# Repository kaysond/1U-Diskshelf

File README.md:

# 1U-DiskShelf
A 3D-Printable 1U Disk Shelf (4 bays) With Custom SATA Backplane

Board files can be found in the Backplane PCB directory.

Models can be found on [MakerWorld](https://makerworld.com/en/models/1570200-1u-disk-shelf-19-inch-4-bay-10-inch-2-bay) or see the Models directory for CAD files

# License
This project is released under the CC BY-NC-SA 4.0 license. See LICENSE.txt or https://creativecommons.org/licenses/by-nc-sa/4.0/

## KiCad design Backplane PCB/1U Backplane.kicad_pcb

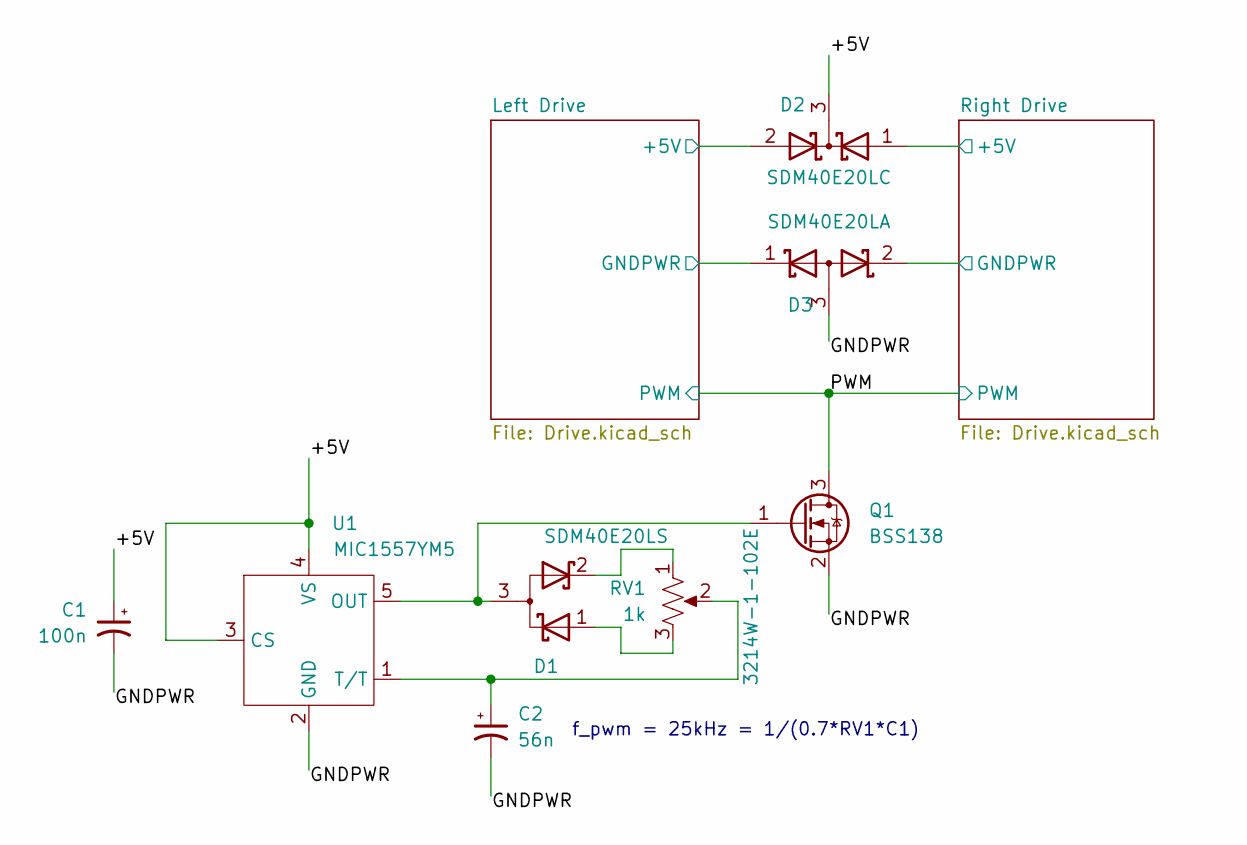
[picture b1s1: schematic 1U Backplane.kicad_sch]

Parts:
C1: 100n; C_0603_1608Metric_Pad1.08x0.95mm_HandSolder
C2: 56n; C_0603_1608Metric_Pad1.08x0.95mm_HandSolder
D1: SDM40E20LS; SOT-23
D2: SDM40E20LC; SOT-23
D3: SDM40E20LA; SOT-23
Q1: BSS138; SOT-23
RV1: 1k; Potentiometer_Bourns_3214W_Vertical; Part No 3214W-1-102E
U1: MIC1557YM5; SOT-23-5

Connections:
/+5V: C1.1, D2.3 (K), U1.3 (CS), U1.4 (VS)
/GNDPWR: C1.2, C2.2, D3.3 (A), Q1.2 (S), U1.2 (GND)
/Left Drive/+5V: D2.2 (A); also elsewhere on the board
/Left Drive/GNDPWR: D3.1 (K); also elsewhere on the board
/PWM: Q1.3 (D); also elsewhere on the board
/Right Drive/+5V: D2.1 (A); also elsewhere on the board
/Right Drive/GNDPWR: D3.2 (K); also elsewhere on the board
unnamed: D1.3 (A), Q1.1 (G), U1.5 (OUT)
unnamed: D1.1 (K), RV1.3
unnamed: D1.2 (K), RV1.1
unnamed: C2.1, RV1.2, U1.1 (T/T)

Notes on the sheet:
f_pwm = 25kHz = 1/(0.7*RV1*C1)

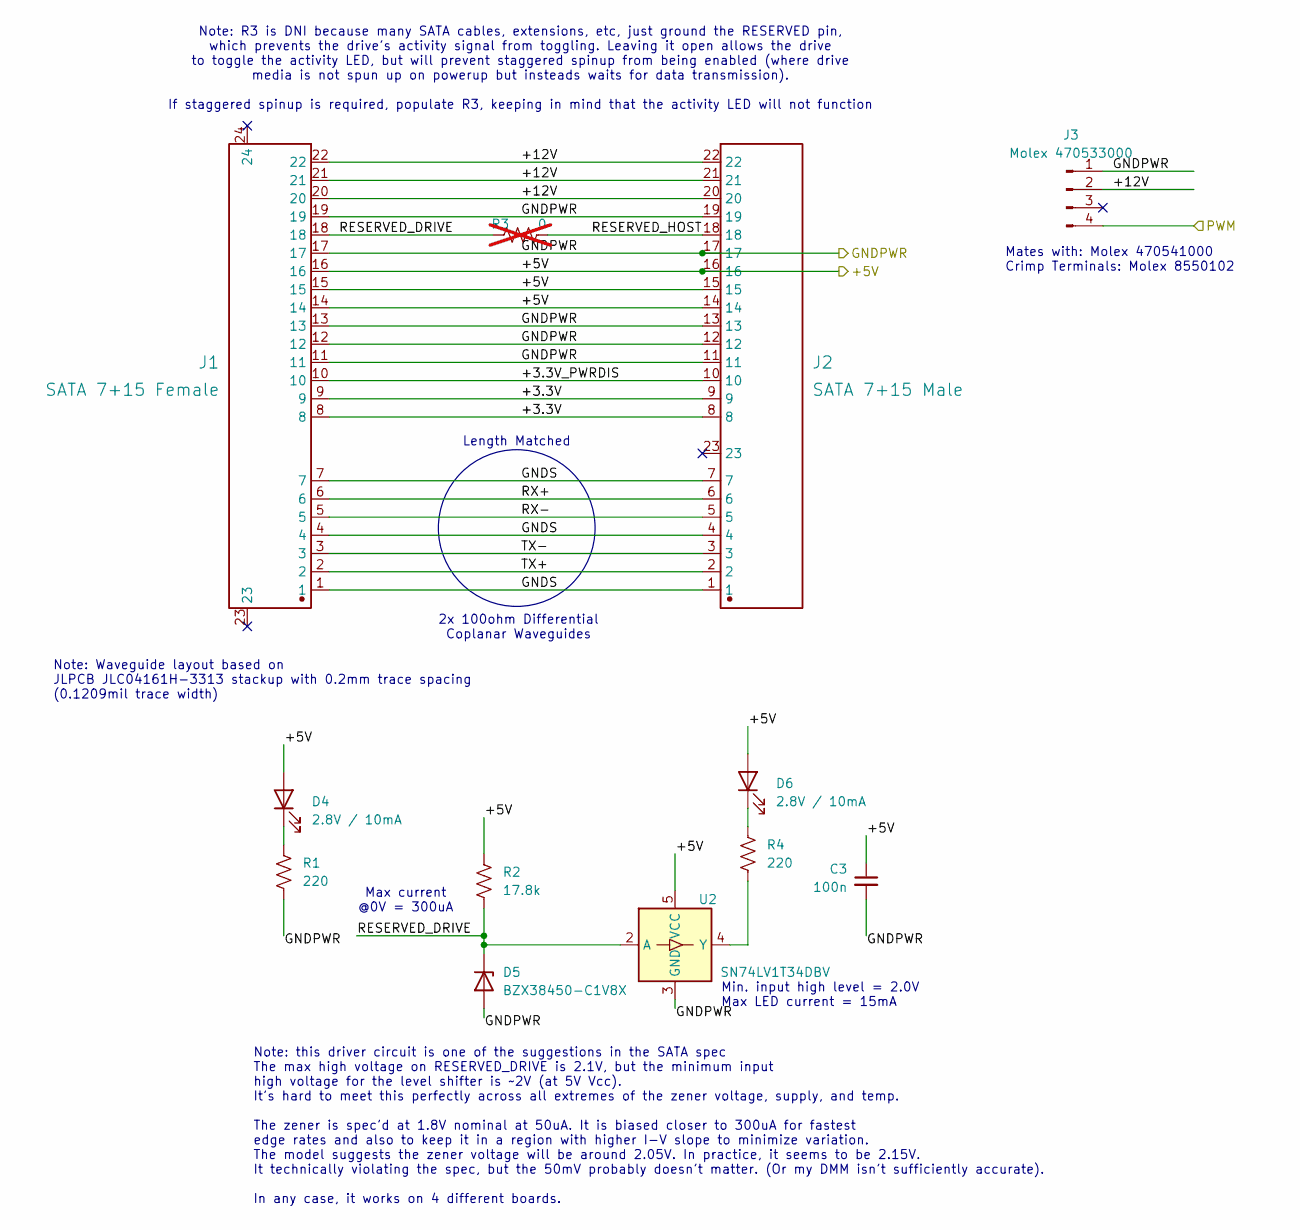
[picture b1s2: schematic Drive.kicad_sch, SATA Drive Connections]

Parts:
C3: 100n; C_0603_1608Metric_Pad1.08x0.95mm_HandSolder
D4, D6: 2.8V / 10mA; LED_0603_1608Metric_Pad1.05x0.95mm_HandSolder
D5: BZX38450-C1V8X; D_SOD-323_HandSoldering
J1: SATA 7+15 Female; CONN-TH_SATA7-15-TYPE-B; Manufacturer Part SATA 7+15 TYPE-B
J2: SATA 7+15 Male; CONN-TH_SATA7-15-TYPE-A; Manufacturer Part SATA 7+15 TYPE-A
J3: Molex 470533000; Molex_KK-254_AE-6410-04A_1x04_P2.54mm_Vertical
R1, R4: 220; R_0603_1608Metric_Pad0.98x0.95mm_HandSolder
R2: 17.8k; R_0603_1608Metric_Pad0.98x0.95mm_HandSolder
R3: 0; R_0402_1005Metric; not fitted
U2: SN74LV1T34DBV; SOT-23-5

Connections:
/Left Drive/+3.3V: J1.8, J1.9, J2.8, J2.9
/Left Drive/+3.3V_PWRDIS: J1.10, J2.10
/Left Drive/+5V: C3.1, D4.2 (A), D6.2 (A), J1.14, J1.15, J1.16, J2.14, J2.15, J2.16, R2.1, U2.5 (VCC); also elsewhere on the board
/Left Drive/+12V: J1.20, J1.21, J1.22, J2.20, J2.21, J2.22, J3.2
/Left Drive/GNDPWR: C3.2, D5.2 (A), J1.11, J1.12, J1.13, J1.17, J1.19, J2.11, J2.12, J2.13, J2.17, J2.19, J3.1, R1.2, U2.3 (GND); also elsewhere on the board
/Left Drive/GNDS: J1.1, J1.4, J1.7, J2.1, J2.4, J2.7
/Left Drive/RESERVED_DRIVE: D5.1 (K), J1.18, R2.2, R3.1, U2.2 (A)
/Left Drive/RESERVED_HOST: J2.18, R3.2
/Left Drive/RX+: J1.6, J2.6
/Left Drive/RX-: J1.5, J2.5
/Left Drive/TX+: J1.2, J2.2
/Left Drive/TX-: J1.3, J2.3
/PWM: J3.4; also elsewhere on the board
unnamed: D4.1 (K), R1.1
unnamed: D6.1 (K), R4.1
unnamed: R4.2, U2.4 (Y)

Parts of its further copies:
C4: 100n; C_0603_1608Metric_Pad1.08x0.95mm_HandSolder
D7, D9: 2.8V / 10mA; LED_0603_1608Metric_Pad1.05x0.95mm_HandSolder
D8: BZX38450-C1V8X; D_SOD-323_HandSoldering
J4: SATA 7+15 Female; CONN-TH_SATA7-15-TYPE-B; Manufacturer Part SATA 7+15 TYPE-B
J5: SATA 7+15 Male; CONN-TH_SATA7-15-TYPE-A; Manufacturer Part SATA 7+15 TYPE-A
J6: Molex 470533000; Molex_KK-254_AE-6410-04A_1x04_P2.54mm_Vertical
R5, R8: 220; R_0603_1608Metric_Pad0.98x0.95mm_HandSolder
R6: 17.8k; R_0603_1608Metric_Pad0.98x0.95mm_HandSolder
R7: 0; R_0402_1005Metric; not fitted
U3: SN74LV1T34DBV; SOT-23-5

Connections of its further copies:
/PWM: J6.4; also elsewhere on the board
/Right Drive/+3.3V: J4.8, J4.9, J5.8, J5.9
/Right Drive/+3.3V_PWRDIS: J4.10, J5.10
/Right Drive/+5V: C4.1, D7.2 (A), D9.2 (A), J4.14, J4.15, J4.16, J5.14, J5.15, J5.16, R6.1, U3.5 (VCC); also elsewhere on the board
/Right Drive/+12V: J4.20, J4.21, J4.22, J5.20, J5.21, J5.22, J6.2
/Right Drive/GNDPWR: C4.2, D8.2 (A), J4.11, J4.12, J4.13, J4.17, J4.19, J5.11, J5.12, J5.13, J5.17, J5.19, J6.1, R5.2, U3.3 (GND); also elsewhere on the board
/Right Drive/GNDS: J4.1, J4.4, J4.7, J5.1, J5.4, J5.7
/Right Drive/RESERVED_DRIVE: D8.1 (K), J4.18, R6.2, R7.1, U3.2 (A)
/Right Drive/RESERVED_HOST: J5.18, R7.2
/Right Drive/RX+: J4.6, J5.6
/Right Drive/RX-: J4.5, J5.5
/Right Drive/TX+: J4.2, J5.2
/Right Drive/TX-: J4.3, J5.3
unnamed: D7.1 (K), R5.1
unnamed: D9.1 (K), R8.1
unnamed: R8.2, U3.4 (Y)

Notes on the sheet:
Note: Waveguide layout based on JLPCB JLC04161H-3313 stackup with 0.2mm trace spacing (0.1209mil trace width)
Min. input high level = 2.0V
Note: R3 is DNI because many SATA cables, extensions, etc, just ground the RESERVED pin, which prevents the drive's activity signal from toggling. Leaving it open allows the drive to toggle the activity LED, but will prevent staggered spinup from being enabled (where drive media is not spun up on p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
Length Matched
Max current @0V = 300uA
Max LED current = 15mA
Mates with: Molex 470541000 Crimp Terminals: Molex 8550102
2x 100ohm Differential Coplanar Waveguides
Note: this driver circuit is one of the suggestions in the SATA spec The max high voltage on RESERVED_DRIVE is 2.1V, but the minimum input high voltage for the level shifter is ~2V (at 5V Vcc). It's hard to meet this perfectly across all extremes of the zener voltage, supply, and temp. The zener is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

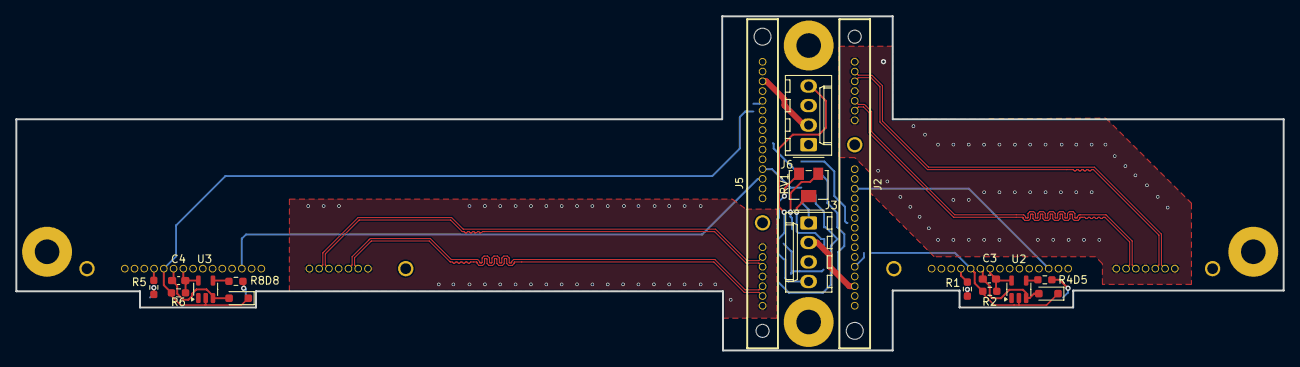
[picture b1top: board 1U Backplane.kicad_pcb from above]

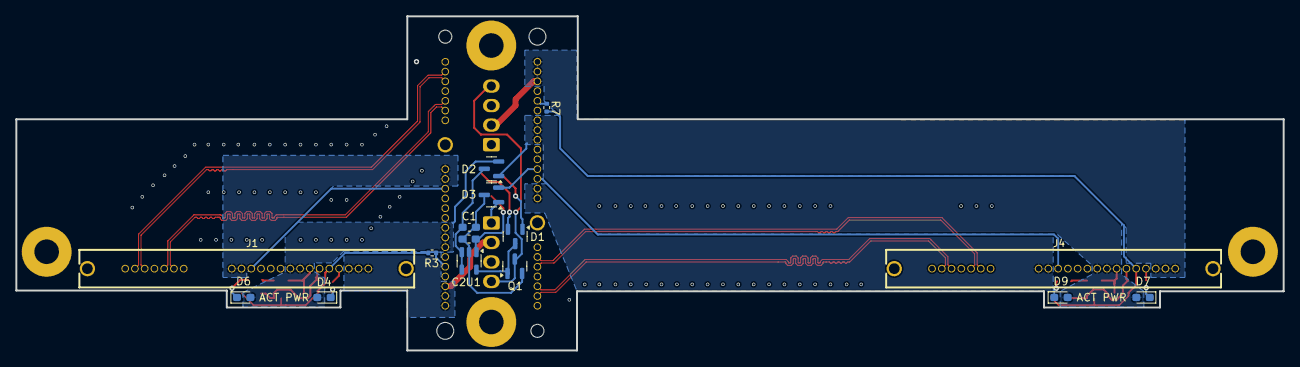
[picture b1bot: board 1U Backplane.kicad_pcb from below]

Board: 4 copper layers, 165.0 x 43.5 mm, 36 parts (15 on the bottom side), 37 nets.

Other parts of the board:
Pad_gge6706, Pad_gge8659, Pad_gge8677, Pad_gge8716: M3 Screw Mount Hole

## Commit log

2025-04-09 Initial commit of PCB design
2025-06-20 Update PCB
2025-07-02 Add CAD models
